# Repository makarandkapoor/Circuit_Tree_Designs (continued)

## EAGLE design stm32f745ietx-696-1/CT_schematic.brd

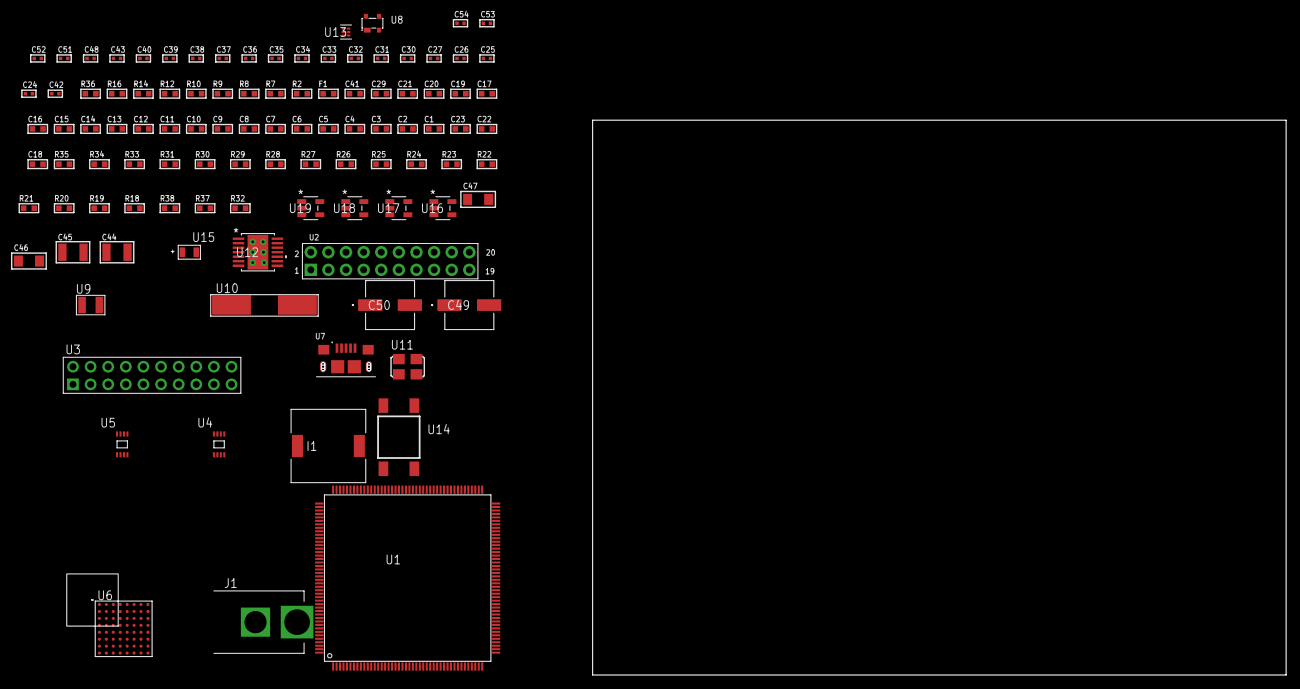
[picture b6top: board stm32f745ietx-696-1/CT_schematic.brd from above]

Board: 2 copper layers, 104 parts (0 on the bottom side), 101 nets, no tracks yet.

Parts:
C1, C20, C29, C41: 1e-06; C0603
C2, C3, C4, C5, C6, C7, C8, C9, C10, C11, C12, C13, C14, C15, C16, C17, C21: 1e-07; C0603
C18: 4.7e-06; C0603
C19: 1e-08; C0603
C22, C23: 2.2e-06; C0603
C24, C25, C26, C27: 1e-11; C0402
C30, C31, C34, C36, C38, C43, C48: 1e-07; C0402
C32, C33, C35, C37, C39, C40, C51, C52, C53, C54: 1e-08; C0402
C42: 3.3e-09; C0402
C44, C45: 2.2e-05; C1210
C46, C47: 1e-05; C1206
C49, C50: 0.0001; EXV-9H
F1: 240.0; L0603
I1: 5.2e-06; DR1040
J1: PJ-037B; PJ-037B_PACKAGE
R2: 1000.0; R0603
R7, R8, R9: 4700.0; R0603
R10, R12, R14, R16: 2200.0; R0603
R18, R19, R20, R21, R22, R23, R24, R25, R26, R27, R28, R29, R30, R31, R34, R35: 10000.0; R0603
R32: 71007.101651032; R0603
R33: 22000.0; R0603
R36: 9100.0; R0603
R37: 680000.0; R0603
R38: 120000.0; R0603
U1: STM32F745IET6; LQFP176
U2: arducam_ov2640; ARDUCAM
U3: TST-110-05-T-D-RA
U4, U5: 24AA00T-I/MNY; TDFN-8/6MM
U6: PC28F512P33BFD
U7: 10118193-0001LF; FCI_10118193-0001LF
U8: prtr5v0u2ax; SOT143B
U9: ABS07-32.768KHZ-7-T
U10: ABLS-25.000MHZ-B2F-T
U11: ASFL1-25MHZ-NCS; ASFL1
U12: tps54225PWP; HTSSOP14
U13: TPS3895ADRYR; SON-6
U14: 4-1437565-2; SW_4-1437565-2
U15: Q65110A2395; LGM67K-G1J2-24-Z
U16, U17, U18, U19: nc7sz125m5x; NC7SZ125M5X

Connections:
CLK_CRYSTAL_U1_9: C24.1, U1.9, U9.1
CLK_CRYSTAL_U1_10: C25.1, U1.10, U9.2
CLK_CRYSTAL_U1_29: C26.1, U1.29, U10.1
CLK_CRYSTAL_U1_30: C27.1, U1.30, U10.2
CLK_U2_8: U2.8, U11.3
GND: C1.2, C2.2, C3.2, C4.2, C5.2, C6.2, C7.2, C8.2, C9.2, C10.2, C11.2, C12.2, C13.2, C14.2, C15.2, C16.2, C17.2, C18.2, C19.2, C20.2, C21.2, C22.2, C23.2, C24.2, C25.2, C26.2, C27.2, C29.2, C30.2, C31.2, C32.2, C33.2, C34.2, C35.2, C36.2, C37.2, C38.2, C39.2, C40.2, C41.2, C42.2, C44.2, C45.2, C46.2, C47.2, C48.2, C49.2, C50.2, C51.2, C52.2, C53.2, C54.2, J1.2, R2.2, R18.2, R20.2, R26.2, R33.2, R36.2, R38.2, U1.14, U1.22, U1.37, U1.61, U1.71, U1.90, U1.102, U1.113, U1.126, U1.135, U1.148, U1.158, U2.2, U2.20, U3.4, U3.6, U3.8, U3.10, U3.12, U3.14, U3.16, U3.18, U3.20, U4.4, U5.4, U6.B2, U6.H2, U6.H4, U6.H6, U7.5, U7.6, U7.7, U7.8, U7.9, U8.1, U11.2, U12.5, U12.8, U12.9, U12.15, U13.2, U15.C, U16.2, U16.3, U17.1, U17.3, U18.1, U18.3, U19.1, U19.3
NET_U1_31: R8.1, U1.31, U18.4
NET_U1_39: C19.1, C20.1, F1.1, U1.38, U1.39
NET_U1_45: R14.1, U1.45, U5.6
NET_U1_46: R16.1, U1.46, U5.5
NET_U1_48: R20.1, U1.48
NET_U1_81: C22.1, U1.81
NET_U1_125: C23.1, U1.125
NET_U1_164: R10.1, U1.164, U4.6
NET_U1_166: R18.1, U1.166
NET_U1_168: R12.1, U1.168, U4.5
NET_U1_171: R19.1, U1.171
NET_U1_175: U14.3, U14.4
NET_U2_19: R9.1, U2.19, U19.4
NET_U3_19: R26.1, U3.19
NET_U6_A4: C38.1, C39.1, U6.A4
NET_U6_C6: R30.1, U6.C6
NET_U6_D4: R7.1, U6.D4, U17.4
NET_U12_2: R32.2, R33.1, U12.2
NET_U12_3: C41.1, U12.3
NET_U12_4: C42.1, U12.4
NET_U12_10: C43.1, I1.1, U12.10, U12.11
NET_U12_12: C43.2, U12.12
NET_U13_1: R35.1, R36.1, U13.1
NET_U13_3: R37.2, R38.1, U13.3
NET_U13_4: R34.1, U13.4, U16.4, U17.2, U18.2, U19.2
NET_U14_1: R2.1, U14.1, U14.2
PROC_DCMI_D0: U1.86, U2.18
PROC_DCMI_D1: U1.87, U2.17
PROC_DCMI_D2: U1.88, U2.16
PROC_DCMI_D3: U1.89, U2.15
PROC_DCMI_D4: U1.129, U2.14
PROC_DCMI_D5: U1.173, U2.13
PROC_DCMI_D6: U1.167, U2.12
PROC_DCMI_D7: U1.176, U2.11
PROC_DCMI_D8: U1.83, U2.10
PROC_DCMI_D9: U1.84, U2.9
PROC_DCMI_HSYNC: U1.50, U2.6
PROC_DCMI_PIXCLK: U1.52, U2.7
PROC_DCMI_VSYNC: U1.152, U2.5
PROC_FMC_A0: U1.16, U6.A1
PROC_FMC_A1: U1.17, U6.B1
PROC_FMC_A2: U1.18, U6.C1
PROC_FMC_A3: U1.19, U6.D1
PROC_FMC_A4: U1.20, U6.D2
PROC_FMC_A5: U1.21, U6.A2
PROC_FMC_A6: U1.60, U6.C2
PROC_FMC_A9: U1.65, U6.C3
PROC_FMC_A10: U1.66, U6.D3
PROC_FMC_A11: U1.67, U6.C4
PROC_FMC_A12: U1.106, U6.A5
PROC_FMC_A13: U1.107, U6.B5
PROC_FMC_A14: U1.108, U6.C5
PROC_FMC_A15: U1.109, U6.D7
PROC_FMC_A16: U1.99, U6.D8
PROC_FMC_A17: U1.100, U6.A7
PROC_FMC_A18: U1.101, U6.B7
PROC_FMC_A19: U1.2, U6.C7
PROC_FMC_A20: U1.3, U6.C8
PROC_FMC_A21: U1.4, U6.A8
PROC_FMC_A22: U1.5, U6.G1
PROC_FMC_A23: U1.1, U6.H8
PROC_FMC_A24: U1.156, U6.B6
PROC_FMC_CLK: U1.145, U6.E6
PROC_FMC_D0: U1.104, U6.F2
PROC_FMC_D1: U1.105, U6.E2
PROC_FMC_D2: U1.142, U6.G3
PROC_FMC_D3: U1.143, U6.E4
PROC_FMC_D4: U1.68, U6.E5
PROC_FMC_D5: U1.69, U6.G5
PROC_FMC_D6: U1.70, U6.G6
PROC_FMC_D7: U1.73, U6.H7
PROC_FMC_D8: U1.74, U6.E1
PROC_FMC_D9: U1.75, U6.E3
PROC_FMC_D10: U1.76, U6.F3
PROC_FMC_D11: U1.77, U6.F4
PROC_FMC_D12: U1.78, U6.F5
PROC_FMC_D13: U1.96, U6.H5
PROC_FMC_D14: U1.97, U6.G7
PROC_FMC_D15: U1.98, U6.E7
PROC_FMC_NE2: R28.1, U1.155, U6.B4
PROC_FMC_NL: R27.1, U1.165, U6.F6
PROC_FMC_NOE: R29.1, U1.146, U6.F8
PROC_FMC_NWAIT: U1.150, U6.F7
PROC_FMC_NWE: R31.1, U1.147, U6.G8
PROC_SYS_JTCK_SWCLK: R24.1, U1.137, U3.9
PROC_SYS_JTDI: R22.1, U1.138, U3.5
PROC_SYS_JTDO_SWO: U1.161, U3.13
PROC_SYS_JTMS_SWDIO: R23.1, U1.124, U3.7
PROC_SYS_JTRST: R21.1, U1.162, U3.3
PROC_USB_OTG_FS_DM: U7.2, U8.3
PROC_USB_OTG_FS_DP: U7.3, U8.2
PROC_USB_OTG_FS_VBUS: U7.1, U8.4
RST_OUT_U3_SRESET_B: R25.1, U3.15, U16.1
VCC_S1_7V1: C46.1, C47.1, C49.1, C50.1, J1.1, U12.7, U12.13, U12.14
VCC_TIER1_3V3: C1.1, C2.1, C3.1, C4.1, C5.1, C6.1, C7.1, C8.1, C9.1, C10.1, C11.1, C12.1, C13.1, C14.1, C15.1, C16.1, C17.1, C18.1, C21.1, C29.1, C30.1, C31.1, C32.1, C33.1, C34.1, C35.1, C36.1, C37.1, C40.1, C44.1, C45.1, C48.1, C51.1, C52.1, C53.1, C54.1, F1.2, I1.2, R7.2, R8.2, R9.2, R10.2, R12.2, R14.2, R16.2, R19.2, R21.2, R22.2, R23.2, R24.2, R25.2, R27.2, R28.2, R29.2, R30.2, R31.2, R32.1, R34.2, R35.2, R37.1, U1.6, U1.15, U1.23, U1.36, U1.49, U1.62, U1.72, U1.82, U1.91, U1.103, U1.114, U1.127, U1.136, U1.149, U1.159, U1.172, U2.1, U3.1, U3.2, U4.8, U5.8, U6.A6, U6.D5, U6.D6, U6.G4, U6.H3, U11.4, U12.1, U13.6, U16.5, U17.5, U18.5, U19.5

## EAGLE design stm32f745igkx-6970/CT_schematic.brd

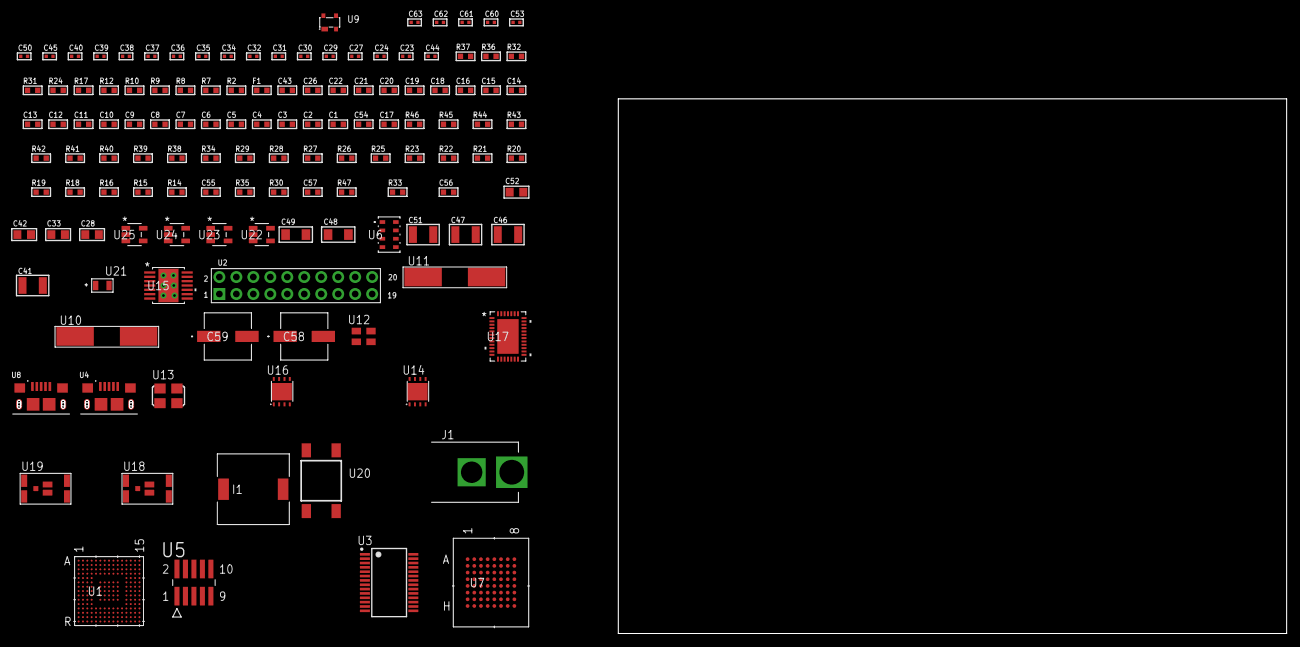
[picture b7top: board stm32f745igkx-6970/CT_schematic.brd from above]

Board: 2 copper layers, 130 parts (0 on the bottom side), 128 nets, no tracks yet.

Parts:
C1, C19, C26, C43: 1e-06; C0603
C2, C3, C4, C5, C6, C7, C8, C9, C10, C11, C12, C13, C14, C15, C16, C20, C21, C22: 1e-07; C0603
C17: 4.7e-06; C0603
C18: 1e-08; C0603
C23, C24: 1e-11; C0402
C27, C29, C30, C31, C32, C34, C35, C45, C53: 1e-07; C0402
C28: 4.7e-06; C0805
C33, C42, C52: 1e-05; C0805
C36, C37, C38, C39, C40, C50, C60, C61, C62, C63: 1e-08; C0402
C41, C51: 1e-05; C1210
C44: 3.3e-09; C0402
C46, C47: 2.2e-05; C1210
C48, C49: 1e-05; C1206
C54: 2.2e-06; C0603
C55: 2.45e-08; R0603
C56: 2.8258362168397e-09; R0603
C57: 7.105e-09; R0603
C58, C59: 0.0001; EXV-9H
F1: 240.0; L0603
I1: 7e-06; DR1040
J1: PJ-037B; PJ-037B_PACKAGE
R2, R32, R37: 1000.0; R0603
R7, R8, R9, R17: 4700.0; R0603
R10, R12: 2200.0; R0603
R14, R15, R16, R18, R19, R20, R21, R22, R23, R25, R26, R27, R28, R29, R38, R40, R41, R44, R45, R46: 10000.0; R0603
R24: 5.0; R0603
R30, R35: 100000.0; R0603
R31, R36: 200.0; R0603
R33: 71007.101651032; R0603
R34: 22000.0; R0603
R39: 75000.0; R0603
R42, R43: 95300.0; R0603
R47: 112254.54545455; R0603
U1: STM32F745IGK6; UFBGA176_25
U2: arducam_ov2640; ARDUCAM
U3: FT232RL-REEL; SSOP-28
U4, U8: 10118193-0001LF; FCI_10118193-0001LF
U5: FTSH-105-01-L-DV-K; SAMTEC_FTSH-105-01-L-DV-K
U6: MPL3115A2R1; LGA-8
U7: mt28ew512aba1HPC-0AAT; LBGA-64
U9: prtr5v0u2ax; SOT143B
U10: ABLS-25.000MHZ-B2F-T
U11: ABLS-12.000MHZ-B4-T
U12: ASEK-32.768KHz-ECST; ASEK
U13: ASFL1-25MHZ-NCS; ASFL1
U14, U16: LP3878SDX-ADJ/NOPB; WSON-8
U15: tps54225PWP; HTSSOP14
U17: LTC2928CUHF#PBF; QFN-38_UHF
U18, U19: IRF8306MTRPbF; IRF8306MTRPBF
U20: 4-1437565-2; SW_4-1437565-2
U21: Q65110A2395; LGM67K-G1J2-24-Z
U22, U23, U24, U25: nc7sz125m5x; NC7SZ125M5X

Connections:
CLK_CRYSTAL_U1_G1: C23.1, U1.G1, U10.1
CLK_CRYSTAL_U1_H1: C24.1, U1.H1, U10.2
CLK_CRYSTAL_U3_27: U3.27, U11.1
CLK_CRYSTAL_U3_28: U3.28, U11.2
CLK_U1_E1: U1.E1, U12.3
CLK_U2_8: U2.8, U13.3
GND: C1.2, C2.2, C3.2, C4.2, C5.2, C6.2, C7.2, C8.2, C9.2, C10.2, C11.2, C12.2, C13.2, C14.2, C15.2, C16.2, C17.2, C18.2, C19.2, C20.2, C21.2, C22.2, C23.2, C24.2, C26.2, C27.2, C28.2, C29.2, C30.2, C31.2, C32.2, C33.2, C34.2, C35.2, C36.2, C37.2, C38.2, C39.2, C40.2, C41.2, C42.2, C43.2, C44.2, C46.2, C47.2, C48.2, C49.2, C50.2, C51.2, C52.2, C53.2, C54.2, C55.2, C56.2, C57.2, C58.2, C59.2, C60.2, C61.2, C62.2, C63.2, J1.2, R2.2, R14.2, R19.2, R23.2, R24.2, R32.2, R34.2, R37.2, R39.2, R42.2, R43.2, R44.2, R45.2, R46.2, U1.D5, U1.D7, U1.D8, U1.D9, U1.F2, U1.F6, U1.F7, U1.F8, U1.F9, U1.F10, U1.F12, U1.G2, U1.G6, U1.G7, U1.G8, U1.G9, U1.G10, U1.G12, U1.H6, U1.H7, U1.H8, U1.H9, U1.H10, U1.H12, U1.J6, U1.J7, U1.J8, U1.J9, U1.J10, U1.K6, U1.K7, U1.K8, U1.K9, U1.K10, U1.M1, U1.M8, U1.M9, U1.N1, U2.2, U2.20, U3.7, U3.18, U3.21, U3.25, U3.26, U4.5, U4.6, U4.7, U4.8, U4.9, U5.3, U5.5, U6.3, U7.E8, U7.H2, U7.H7, U8.5, U8.6, U8.7, U8.8, U8.9, U9.1, U12.2, U13.2, U14.3, U14.PAD, U15.5, U15.8, U15.9, U15.15, U16.3, U16.PAD, U17.8, U17.9, U17.10, U17.12, U17.13, U17.24, U17.25, U17.30, U17.32, U17.39, U21.C, U22.2, U22.3, U23.1, U23.3, U24.1, U24.3, U25.1, U25.3
NET_U1_A5: R10.1, U1.A5, U6.8
NET_U1_B4: R12.1, U1.B4, U6.7
NET_U1_C6: R15.1, U1.C6
NET_U1_D6: R14.1, U1.D6
NET_U1_F13: C22.1, U1.F13
NET_U1_J1: R8.1, U1.J1, U24.4
NET_U1_L4: R16.1, U1.L4
NET_U1_R1: C18.1, C19.1, F1.1, U1.P1, U1.R1
NET_U1_R15: U20.3, U20.4
NET_U2_19: R9.1, U2.19, U25.4
NET_U3_14: R18.1, U3.14
NET_U3_17: C29.1, U3.17
NET_U3_19: R19.1, U3.19
NET_U4_1: R17.1, U4.1
NET_U4_2: U3.16, U4.2
NET_U4_3: U3.15, U4.3
NET_U5_9: R24.1, U5.9
NET_U6_2: C35.1, U6.2
NET_U7_B4: R28.1, U7.B4
NET_U7_B5: R7.1, U7.B5, U23.4
NET_U14_1: C40.1, U14.1
NET_U14_6: R31.2, R32.1, U14.6
NET_U14_8: R30.1, U14.8
NET_U15_2: R33.2, R34.1, U15.2
NET_U15_3: C43.1, U15.3
NET_U15_4: C44.1, U15.4
NET_U15_10: C45.1, I1.1, U15.10, U15.11
NET_U15_12: C45.2, U15.12
NET_U16_1: C50.1, U16.1
NET_U16_6: R36.2, R37.1, U16.6
NET_U16_8: R35.1, U16.8
NET_U17_3: R45.1, U17.3
NET_U17_6: R42.1, U17.6
NET_U17_7: R43.1, U17.7
NET_U17_16: R44.1, R47.1, U17.16
NET_U17_18: R41.1, U17.18
NET_U17_19: R40.1, U17.19, U17.20
NET_U17_21: R38.1, R39.1, U17.21, U22.4, U23.2, U24.2, U25.2
NET_U17_22: C53.1, R38.2, R40.2, R41.2, U17.11, U17.22
NET_U17_26: C56.1, U17.26
NET_U17_27: C55.1, U17.27
NET_U17_28: C57.1, U17.28
NET_U17_38: R46.1, U17.38
NET_U18_3: U17.2, U18.3
NET_U19_3: U17.37, U19.3
NET_U20_1: R2.1, U20.1, U20.2
PROC_DCMI_D0: U1.H15, U2.18
PROC_DCMI_D1: U1.D15, U2.17
PROC_DCMI_D2: U1.B10, U2.16
PROC_DCMI_D3: U1.A3, U2.15
PROC_DCMI_D4: U1.B13, U2.14
PROC_DCMI_D5: U1.B6, U2.13
PROC_DCMI_D6: U1.C3, U2.12
PROC_DCMI_D7: U1.C2, U2.11
PROC_DCMI_D8: U1.B14, U2.10
PROC_DCMI_D9: U1.C14, U2.9
PROC_DCMI_HSYNC: U1.M12, U2.6
PROC_DCMI_PIXCLK: U1.P3, U2.7
PROC_DCMI_VSYNC: U1.B5, U2.5
PROC_FMC_A0: U1.E2, U7.E2
PROC_FMC_A1: U1.H3, U7.D2
PROC_FMC_A2: U1.H2, U7.C2
PROC_FMC_A3: U1.J2, U7.A2
PROC_FMC_A4: U1.J3, U7.B2
PROC_FMC_A5: U1.K3, U7.D3
PROC_FMC_A6: U1.P6, U7.C3
PROC_FMC_A9: U1.P7, U7.A6
PROC_FMC_A10: U1.N7, U7.C6
PROC_FMC_A11: U1.M7, U7.D6
PROC_FMC_A12: U1.L15, U7.B7
PROC_FMC_A13: U1.K15, U7.A7
PROC_FMC_A14: U1.K14, U7.C7
PROC_FMC_A15: U1.K13, U7.D7
PROC_FMC_A16: U1.N14, U7.E7
PROC_FMC_A17: U1.N13, U7.B3
PROC_FMC_A18: U1.M15, U7.C4
PROC_FMC_A19: U1.A1, U7.D5
PROC_FMC_A20: U1.B1, U7.D4
PROC_FMC_A21: U1.B2, U7.C5
PROC_FMC_A22: U1.B3, U7.B8
PROC_FMC_A23: U1.A2, U7.C8
PROC_FMC_A24: U1.A8, U7.F8
PROC_FMC_D0: U1.M14, U7.E3
PROC_FMC_D1: U1.L14, U7.H3
PROC_FMC_D2: U1.B12, U7.E4
PROC_FMC_D3: U1.C12, U7.H4
PROC_FMC_D4: U1.R8, U7.H5
PROC_FMC_D5: U1.P8, U7.E5
PROC_FMC_D6: U1.P9, U7.H6
PROC_FMC_D7: U1.R9, U7.E6
PROC_FMC_D8: U1.P10, U7.F3
PROC_FMC_D9: U1.R10, U7.G3
PROC_FMC_D10: U1.N11, U7.F4
PROC_FMC_D11: U1.P11, U7.G4
PROC_FMC_D12: U1.R11, U7.F5
PROC_FMC_D13: U1.P15, U7.G6
PROC_FMC_D14: U1.P14, U7.F6
PROC_FMC_D15: U1.N15, U7.G7
PROC_FMC_NBL0: R29.1, U1.A4, U7.F7
PROC_FMC_NE2: R25.1, U1.C10, U7.F2
PROC_FMC_NOE: R26.1, U1.D10, U7.G2
PROC_FMC_NWAIT: U1.B11, U7.A4
PROC_FMC_NWE: R27.1, U1.C11, U7.A5
PROC_SYS_JTCK_SWCLK: R23.1, U1.A14, U5.4
PROC_SYS_JTDI: R21.1, U1.A13, U5.8
PROC_SYS_JTDO_SWO: U1.A10, U5.6
PROC_SYS_JTMS_SWDIO: R22.1, U1.A15, U5.2
PROC_UART5_CTS: U1.F14, U3.3
PROC_UART5_RTS: U1.G14, U3.11
PROC_UART5_RX: U1.D12, U3.1
PROC_UART5_TX: U1.A12, U3.5
PROC_USB_OTG_FS_DM: U8.2, U9.3
PROC_USB_OTG_FS_DP: U8.3, U9.2
PROC_USB_OTG_FS_VBUS: U8.1, U9.4
RST_OUT_U5_JTAG_RST_B: R20.1, U5.10, U22.1
VCC_13V7: C54.1, C58.1, C59.1, J1.1, R47.2, U17.23, U18.1, U18.2, U18.6, U18.7, U19.1, U19.2, U19.6, U19.7
VCC_S1_13V7: C41.1, C48.1, C49.1, R30.2, U14.4, U15.7, U15.13, U15.14, U18.4, U18.5
VCC_S2_13V7: C51.1, R35.2, U16.4, U19.4, U19.5
VCC_TIER1_1V2: C21.1, C42.1, R31.1, U1.M10, U14.5
VCC_TIER1_3V3: C1.1, C2.1, C3.1, C4.1, C5.1, C6.1, C7.1, C8.1, C9.1, C10.1, C11.1, C12.1, C13.1, C14.1, C15.1, C16.1, C17.1, C20.1, C26.1, C27.1, C28.1, C30.1, C31.1, C32.1, C33.1, C34.1, C36.1, C37.1, C38.1, C39.1, C46.1, C47.1, C60.1, C61.1, C62.1, C63.1, F1.2, I1.2, R7.2, R8.2, R9.2, R10.2, R12.2, R15.2, R16.2, R18.2, R20.2, R21.2, R22.2, R25.2, R26.2, R27.2, R28.2, R29.2, R33.1, U1.C1, U1.C5, U1.C7, U1.C8, U1.C9, U1.F3, U1.G3, U1.G13, U1.H13, U1.J12, U1.J13, U1.K4, U1.N8, U1.N9, U1.N10, U2.1, U3.4, U3.20, U5.1, U6.1, U6.4, U7.D8, U7.F1, U7.G5, U12.4, U13.4, U15.1, U22.5, U23.5, U24.5, U25.5
VCC_TIER2_1V2: C52.1, R36.1, U16.5

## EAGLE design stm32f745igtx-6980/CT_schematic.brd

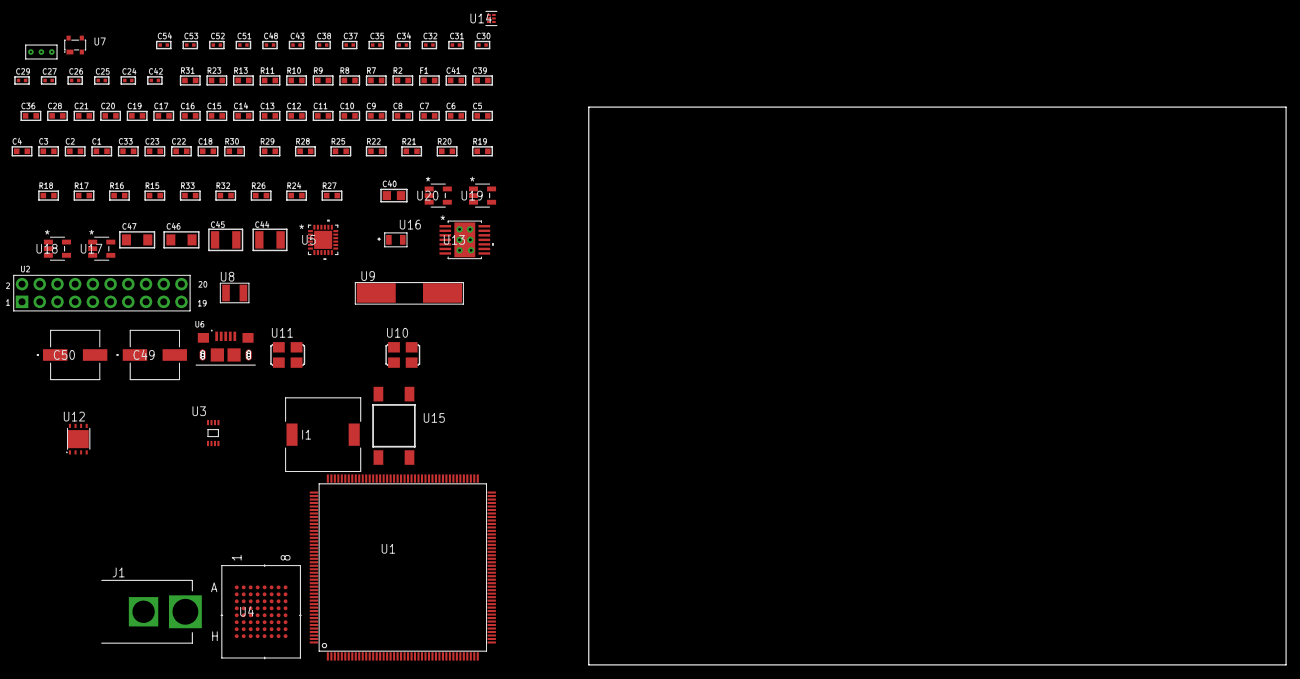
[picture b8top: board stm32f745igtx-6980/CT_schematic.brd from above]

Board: 2 copper layers, 104 parts (0 on the bottom side), 99 nets, no tracks yet.

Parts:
C1, C20, C28, C36, C41: 1e-06; C0603
C2, C3, C4, C5, C6, C7, C8, C9, C10, C11, C12, C13, C14, C15, C16, C17, C21: 1e-07; C0603
C18: 4.7e-06; C0603
C19: 1e-08; C0603
C22, C23, C33: 2.2e-06; C0603
C24, C25, C26, C27: 1e-11; C0402
C29, C30, C31, C32, C34, C35, C37, C38, C51, C52, C53, C54: 1e-08; C0402
C39: 8e-07; R0603
C40: 1e-05; C0805
C42: 3.3e-09; C0402
C43, C48: 1e-07; C0402
C44, C45: 2.2e-05; C1210
C46, C47: 1e-05; C1206
C49, C50: 0.0001; EXV-9H
F1: 240.0; L0603
I1: 7e-06; DR1040
J1: PJ-037B; PJ-037B_PACKAGE
R2: 1000.0; R0603
R7, R8, R9, R10: 4700.0; R0603
R11, R13: 2200.0; R0603
R15, R16, R17, R18, R19, R20, R21, R22, R29, R30: 10000.0; R0603
R23: 8060.0; R0603
R24, R26: 100000.0; R0603
R25: 36000.0; R0603
R27: 71007.101651032; R0603
R28: 22000.0; R0603
R31: 9100.0; R0603
R32: 680000.0; R0603
R33: 120000.0; R0603
U1: STM32F745IGT6; LQFP176
U2: arducam_ov2640; ARDUCAM
U3: 24AA01T-I/MNY; TDFN-8/6MM
U4: mt28ew512aba1HPC-0AAT; LBGA-64
U5: USB3317C-CP-TR; QFN-24
U6: 10118193-0001LF; FCI_10118193-0001LF
U7: prtr5v0u2ax; SOT143B
U8: ABS07-32.768KHZ-7-T
U9: ABLS-25.000MHZ-B2F-T
U10: ASFL1-25MHZ-NCS; ASFL1
U11: ASFL1-26MHZ-NCS; ASFL1
U12: LP2951ACSDX/NOPB; WSON-8
U13: tps54225PWP; HTSSOP14
U14: TPS3895ADRYR; SON-6
U15: 4-1437565-2; SW_4-1437565-2
U16: Q65110A2395; LGM67K-G1J2-24-Z
U17, U18, U19, U20: nc7sz125m5x; NC7SZ125M5X
U21: Dummy; DUMMY_PACKAGE_227

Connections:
CLK_CRYSTAL_U1_9: C24.1, U1.9, U8.1
CLK_CRYSTAL_U1_10: C25.1, U1.10, U8.2
CLK_CRYSTAL_U1_29: C26.1, U1.29, U9.1
CLK_CRYSTAL_U1_30: C27.1, U1.30, U9.2
CLK_U2_8: U2.8, U10.3
CLK_U5_23: U5.23, U11.3
GND: C1.2, C2.2, C3.2, C4.2, C5.2, C6.2, C7.2, C8.2, C9.2, C10.2, C11.2, C12.2, C13.2, C14.2, C15.2, C16.2, C17.2, C18.2, C19.2, C20.2, C21.2, C22.2, C23.2, C24.2, C25.2, C26.2, C27.2, C28.2, C29.2, C30.2, C31.2, C32.2, C33.2, C34.2, C35.2, C36.2, C37.2, C38.2, C39.2, C40.2, C41.2, C42.2, C44.2, C45.2, C46.2, C47.2, C48.2, C49.2, C50.2, C51.2, C52.2, C53.2, C54.2, J1.2, R2.2, R15.2, R17.2, R23.2, R26.2, R28.2, R31.2, R33.2, U1.14, U1.22, U1.37, U1.61, U1.71, U1.90, U1.102, U1.113, U1.126, U1.135, U1.148, U1.158, U2.2, U2.20, U3.4, U3.7, U4.E8, U4.H2, U4.H7, U5.25, U6.5, U6.6, U6.7, U6.8, U6.9, U7.1, U10.2, U11.2, U12.3, U12.4, U12.PAD, U13.5, U13.8, U13.9, U13.15, U14.2, U16.C, U17.1, U17.3, U18.1, U18.3, U19.1, U19.3, U20.1, U20.3, U21.1
NET_U1_31: R8.1, U1.31, U18.4
NET_U1_39: C19.1, C20.1, F1.1, U1.38, U1.39
NET_U1_48: R17.1, U1.48
NET_U1_81: C22.1, U1.81
NET_U1_125: C23.1, U1.125
NET_U1_164: R11.1, U1.164, U3.6
NET_U1_165: R13.1, U1.165, U3.5
NET_U1_166: R15.1, U1.166
NET_U1_171: R16.1, U1.171
NET_U1_176: U15.3, U15.4
NET_U2_19: R9.1, U2.19, U19.4
NET_U4_B4: R21.1, U4.B4
NET_U4_B5: R7.1, U4.B5, U17.4
NET_U5_4: C33.1, U5.4
NET_U5_22: R10.1, U5.22, U20.4
NET_U5_24: R23.1, U5.24
NET_U6_1: C36.1, U5.2, U6.1, U7.4
NET_U6_2: U5.5, U6.2, U7.3
NET_U6_3: U5.6, U6.3, U7.2
NET_U12_5: R24.1, U12.5
NET_U12_7: R25.2, R26.1, U12.7
NET_U13_2: R27.2, R28.1, U13.2
NET_U13_3: C41.1, U13.3
NET_U13_4: C42.1, U13.4
NET_U13_10: C43.1, I1.1, U13.10, U13.11
NET_U13_12: C43.2, U13.12
NET_U14_1: R30.1, R31.1, U14.1
NET_U14_3: R32.2, R33.1, U14.3
NET_U14_4: R29.1, U14.4, U17.2, U18.2, U19.2, U20.2
NET_U15_1: R2.1, U15.1, U15.2
PROC_DCMI_D0: U1.86, U2.18
PROC_DCMI_D1: U1.87, U2.17
PROC_DCMI_D2: U1.88, U2.16
PROC_DCMI_D3: U1.89, U2.15
PROC_DCMI_D4: U1.129, U2.14
PROC_DCMI_D5: U1.145, U2.13
PROC_DCMI_D6: U1.167, U2.12
PROC_DCMI_D7: U1.168, U2.11
PROC_DCMI_D8: U1.83, U2.10
PROC_DCMI_D9: U1.84, U2.9
PROC_DCMI_HSYNC: U1.50, U2.6
PROC_DCMI_PIXCLK: U1.52, U2.7
PROC_DCMI_VSYNC: U1.152, U2.5
PROC_FMC_A0: U1.16, U4.E2
PROC_FMC_A1: U1.17, U4.D2
PROC_FMC_A2: U1.18, U4.C2
PROC_FMC_A3: U1.19, U4.A2
PROC_FMC_A4: U1.20, U4.B2
PROC_FMC_A5: U1.21, U4.D3
PROC_FMC_A6: U1.60, U4.C3
PROC_FMC_A9: U1.65, U4.A6
PROC_FMC_A10: U1.66, U4.C6
PROC_FMC_A11: U1.67, U4.D6
PROC_FMC_A12: U1.106, U4.B7
PROC_FMC_A13: U1.107, U4.A7
PROC_FMC_A14: U1.108, U4.C7
PROC_FMC_A15: U1.109, U4.D7
PROC_FMC_A16: U1.99, U4.E7
PROC_FMC_A17: U1.100, U4.B3
PROC_FMC_A18: U1.101, U4.C4
PROC_FMC_A19: U1.2, U4.D5
PROC_FMC_A20: U1.3, U4.D4
PROC_FMC_A21: U1.4, U4.C5
PROC_FMC_A22: U1.5, U4.B8
PROC_FMC_A23: U1.1, U4.C8
PROC_FMC_A24: U1.156, U4.F8
PROC_FMC_D0: U1.104, U4.E3
PROC_FMC_D1: U1.105, U4.H3
PROC_FMC_D2: U1.142, U4.E4
PROC_FMC_D3: U1.143, U4.H4
PROC_FMC_D4: U1.68, U4.H5
PROC_FMC_D5: U1.69, U4.E5
PROC_FMC_D6: U1.70, U4.H6
PROC_FMC_D7: U1.73, U4.E6
PROC_FMC_D8: U1.74, U4.F3
PROC_FMC_D9: U1.75, U4.G3
PROC_FMC_D10: U1.76, U4.F4
PROC_FMC_D11: U1.77, U4.G4
PROC_FMC_D12: U1.78, U4.F5
PROC_FMC_D13: U1.96, U4.G6
PROC_FMC_D14: U1.97, U4.F6
PROC_FMC_D15: U1.98, U4.G7
PROC_FMC_NBL0: R22.1, U1.169, U4.F7
PROC_FMC_NE2: R18.1, U1.155, U4.F2
PROC_FMC_NOE: R19.1, U1.146, U4.G2
PROC_FMC_NWAIT: U1.150, U4.A4
PROC_FMC_NWE: R20.1, U1.147, U4.A5
PROC_PC13: U1.8, U21.3
PROC_PI8: U1.7, U21.2
VCC_S1_12V0: C39.1, C46.1, C47.1, C49.1, C50.1, J1.1, U12.8, U13.7, U13.13, U13.14
VCC_TIER1_1V8: C35.1, C40.1, C51.1, C52.1, C53.1, C54.1, R24.2, R25.1, U5.21, U12.1, U17.5, U18.5, U19.5, U20.5
VCC_TIER1_3V3: C1.1, C2.1, C3.1, C4.1, C5.1, C6.1, C7.1, C8.1, C9.1, C10.1, C11.1, C12.1, C13.1, C14.1, C15.1, C16.1, C17.1, C18.1, C21.1, C28.1, C29.1, C30.1, C31.1, C32.1, C34.1, C37.1, C38.1, C44.1, C45.1, C48.1, F1.2, I1.2, R7.2, R8.2, R9.2, R10.2, R11.2, R13.2, R16.2, R18.2, R19.2, R20.2, R21.2, R22.2, R27.1, R29.2, R30.2, R32.1, U1.6, U1.15, U1.23, U1.36, U1.49, U1.62, U1.72, U1.82, U1.91, U1.103, U1.114, U1.127, U1.136, U1.149, U1.159, U1.172, U2.1, U3.8, U4.D8, U4.F1, U4.G5, U5.3, U5.17, U10.4, U11.4, U13.1, U14.6
